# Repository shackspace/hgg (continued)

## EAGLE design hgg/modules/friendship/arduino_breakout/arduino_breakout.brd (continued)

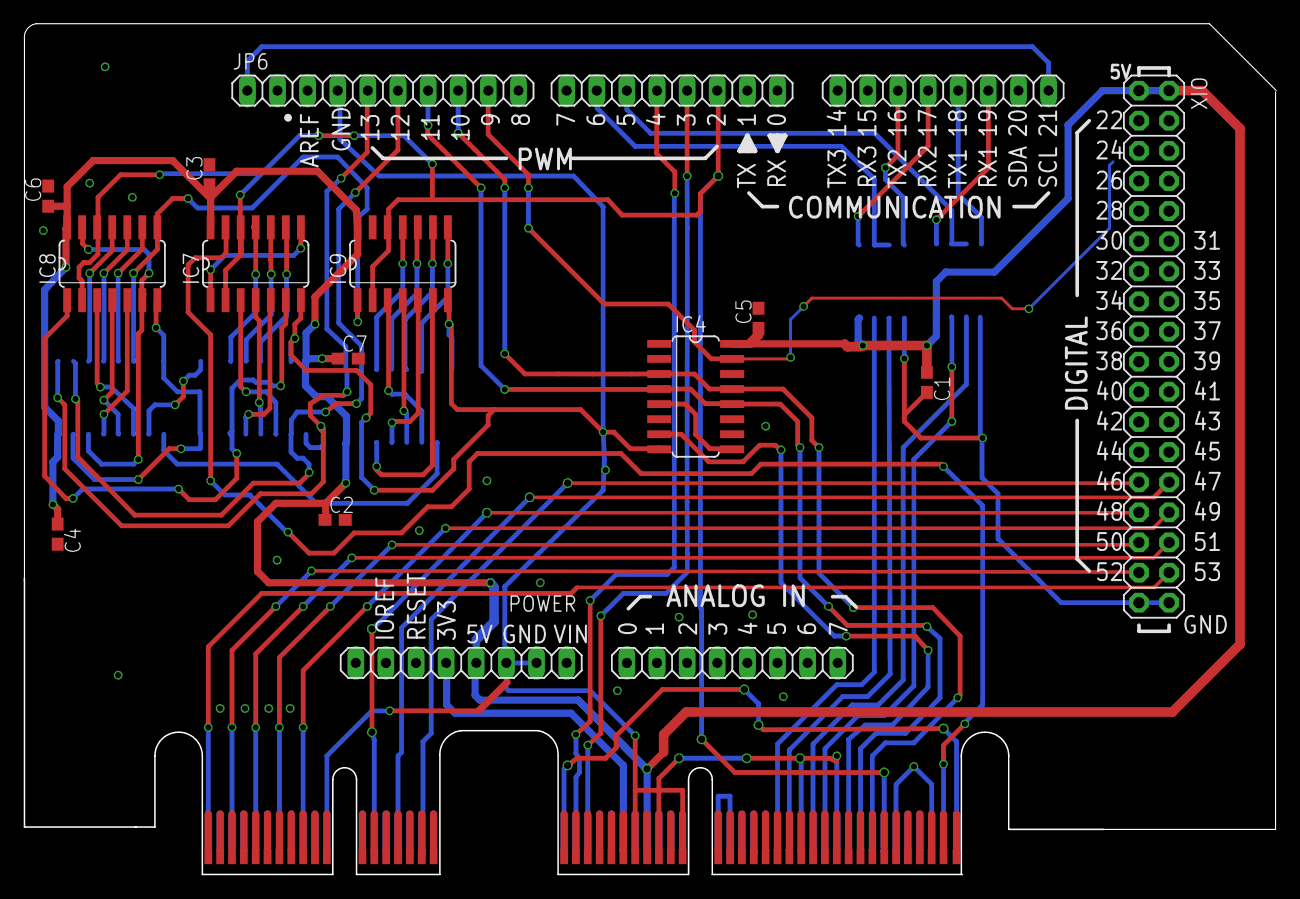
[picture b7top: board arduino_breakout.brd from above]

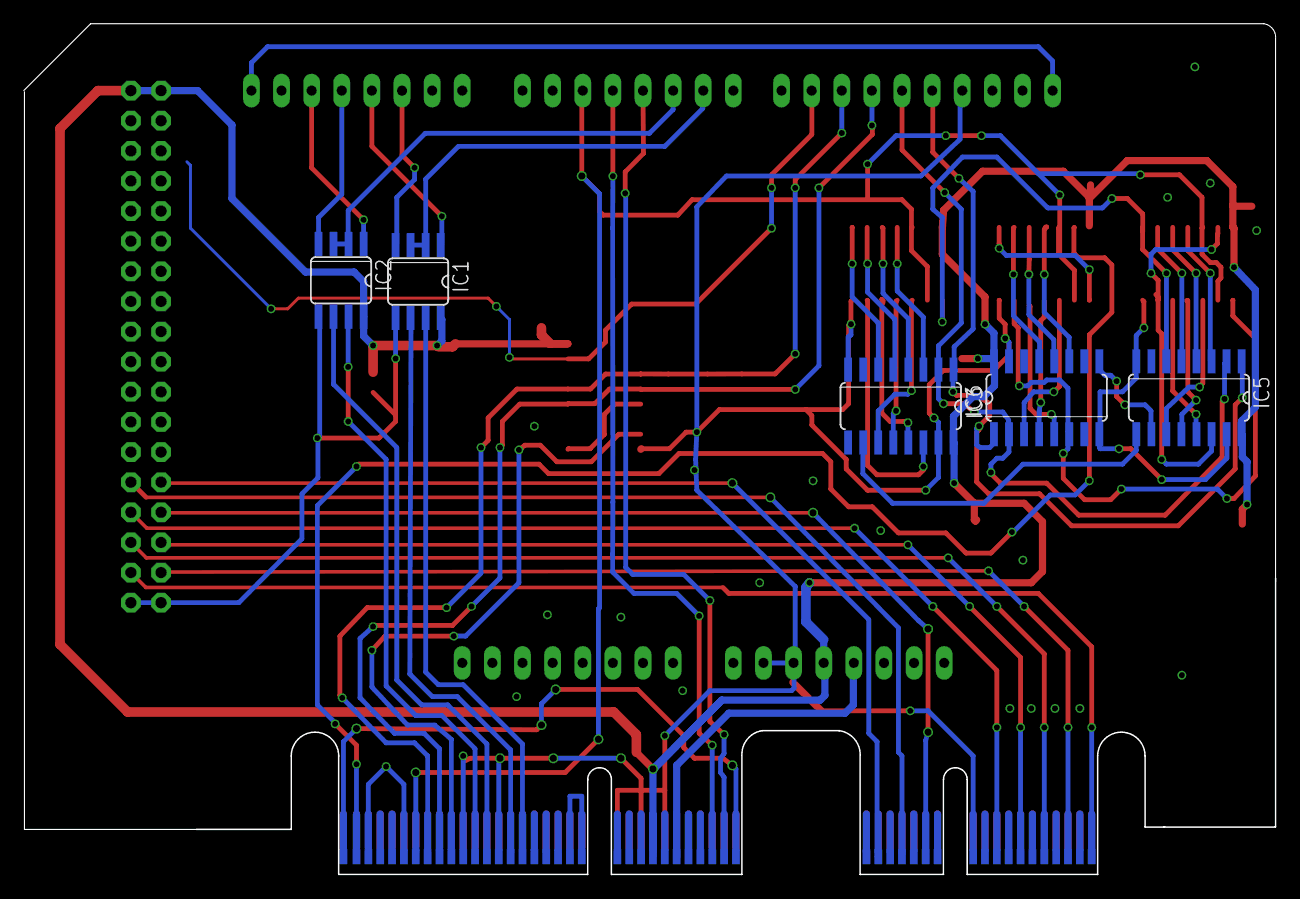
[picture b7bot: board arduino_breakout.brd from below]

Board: 2 copper layers, 105.6 x 71.7 mm, 23 parts (5 on the bottom side), 61 nets.

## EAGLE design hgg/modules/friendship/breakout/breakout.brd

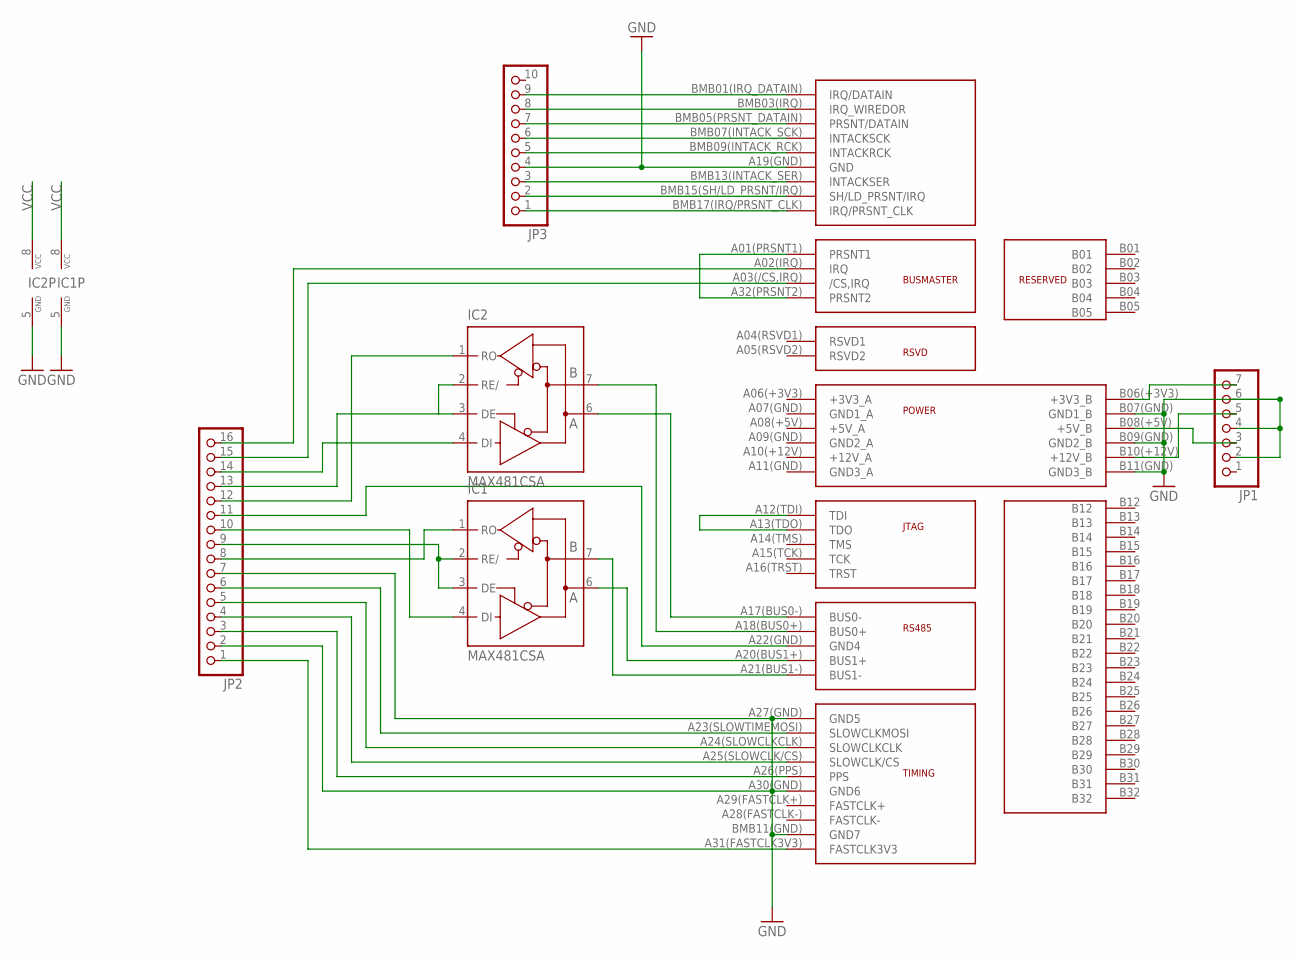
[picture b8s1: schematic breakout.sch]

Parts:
IC1, IC2: MAX481CSA; SO08
JP1: PINHD-1X7; 1X07
JP2: PINHD-1X16; 1X16
JP3: PINHD-1X10; 1X10
U$1: BUSMASTER; BUSMASTER_EDGE_CONNECTOR

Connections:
3V3: JP1.7, U$1.B06(+3V3) (+3V3_B)
12V: JP1.5, U$1.B10(+12V) (+12V_B)
GND: IC1.5 (GND), IC2.5 (GND), JP1.2, JP1.4, JP1.6, JP2.2, JP2.7, JP3.4, U$1.A19(GND) (GND), U$1.A27(GND) (GND5), U$1.A30(GND) (GND6), U$1.B07(GND) (GND1_B), U$1.B09(GND) (GND2_B), U$1.B11(GND) (GND3_B), U$1.BMB11(GND) (GND7)
unnamed: U$1.A01(PRSNT1) (PRSNT1), U$1.A32(PRSNT2) (PRSNT2)
unnamed: IC2.6 (A), U$1.A17(BUS0-) (BUS0-)
unnamed: IC2.7 (B), U$1.A18(BUS0+) (BUS0+)
unnamed: IC2.2 (RE/), IC2.3 (DE), JP2.13
unnamed: JP2.16, U$1.A02(IRQ) (IRQ)
unnamed: JP2.15, U$1.A03(/CS,IRQ) (/CS,IRQ)
unnamed: IC1.6 (A), U$1.A20(BUS1+) (BUS1+)
unnamed: IC2.4 (DI), JP2.14
unnamed: IC1.7 (B), U$1.A21(BUS1-) (BUS1-)
unnamed: JP2.11, U$1.A22(GND) (GND4)
unnamed: IC1.2 (RE/), IC1.3 (DE), JP2.9
unnamed: U$1.A12(TDI) (TDI), U$1.A13(TDO) (TDO)
unnamed: JP3.1, U$1.BMB17(IRQ/PRSNT_CLK) (IRQ/PRSNT_CLK)
unnamed: IC2.1 (RO), JP2.12
unnamed: IC1.1 (RO), JP2.8
unnamed: IC1.4 (DI), JP2.10
unnamed: JP2.6, U$1.A23(SLOWTIMEMOSI) (SLOWCLKMOSI)
unnamed: JP3.2, U$1.BMB15(SH/LD_PRSNT/I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 (SH/LD_PRSNT/IRQ)
unnamed: JP2.5, U$1.A24(SLOWCLKCLK) (SLOWCLKCLK)
unnamed: JP2.4, U$1.A25(SLOWCLK/CS) (SLOWCLK/CS)
unnamed: JP2.3, U$1.A26(PPS) (PPS)
unnamed: JP3.3, U$1.BMB13(INTACK_SER) (INTACKSER)
unnamed: JP2.1, U$1.A31(FASTCLK3V3) (FASTCLK3V3)
unnamed: JP3.5, U$1.BMB09(INTACK_RCK) (INTACKRCK)
unnamed: JP3.6, U$1.BMB07(INTACK_SCK) (INTACKSCK)
unnamed: JP3.7, U$1.BMB05(PRSNT_DATAIN) (PRSNT/DATAIN)
unnamed: JP3.8, U$1.BMB03(IRQ) (IRQ_WIREDOR)
unnamed: JP3.9, U$1.BMB01(IRQ_DATAIN) (IRQ/DATAIN)
VCC: IC1.8 (VCC), IC2.8 (VCC), JP1.3, U$1.B08(+5V) (+5V_B)

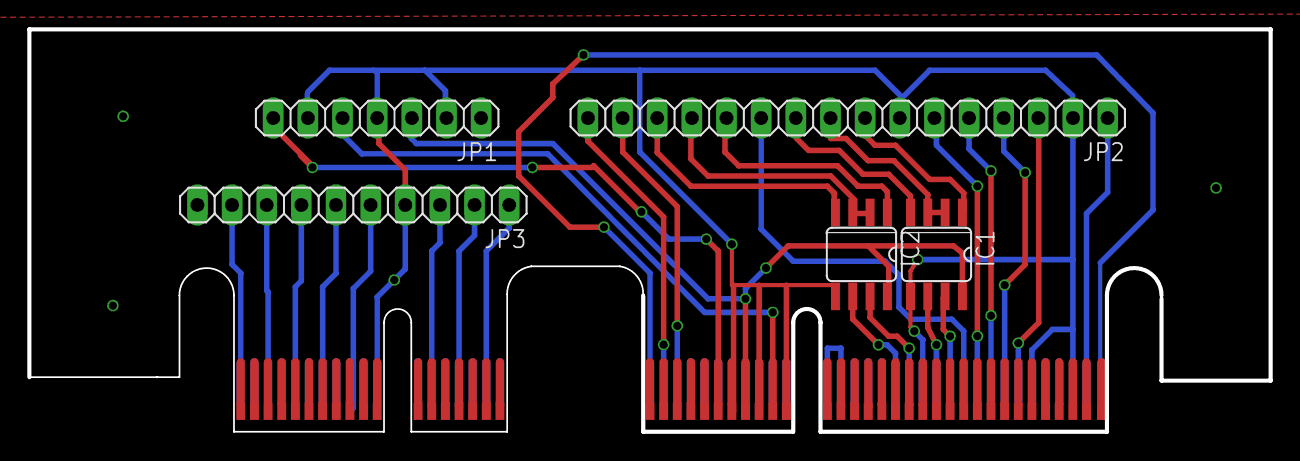
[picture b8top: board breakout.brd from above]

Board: 2 copper layers, 91.0 x 29.5 mm, 6 parts (0 on the bottom side), 32 nets.

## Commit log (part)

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2011-11-01 added dcf77 clocksource
2011-11-01 some tweaks and bugfixes so that the software finds the timings better
2011-11-01 added some more documentation
2011-11-01 added the README
2011-11-01 added some primitive code for dcf77 decoding. It's missing performance, does not perform consistency checks and was made just for proof of concept.
2011-11-20 we can haz better dcf77.
2011-11-20 test
2011-11-20 notes on getting it to work is more verbose.
2011-11-27 gauss loesungsalgorithmus von andreas eingecheckt.
2011-12-29 documentation linked in readme
2012-01-17 to -> too :)
2012-02-05 new version of flutter module, initial version, compiles vhdl nwo
2012-02-05 correct bit counts
2012-02-05 initial commit: schematic and layout of timing fpga board (unfished)
2012-02-05 added reference design: sparkfun fpga breakoutboard
2012-02-09 schematic for power board
2012-02-09 started working on braeburn board design
2012-02-09 routing optimization
2012-02-10 working on schematic: voltage regulators are completed, working on JTAG Port
2012-02-11 added PCIe-X-4 Connector for friendship
2012-02-11 initial version of PCI-e x4 edge connector added
2012-02-11 done for now
2012-02-15 minor change: analog groundplane has a bit more distance to the other groundplanes.
2012-02-16 added tool for utc / unixtime conversion
2012-02-17 fixed my fail on use of a zdiode (thanks to samuel), and stuff
2012-02-18 added logos
2012-02-25 friendship edge connector final
2012-02-26 we started working on friendship schematics
2012-02-26 as far as i got tonight
2012-02-28 bugfix
2012-03-03 Added friendship connector to board and changed FPGA type from XC3S50VQ100 to XC3S50AVQ100
2012-03-09 removed dublicate pinmappings
2012-03-17 changed pinouts around and rounted friendship
2012-03-18 connected FPGA to friendship connector
2012-03-25 added atmega8 to flutter board
2012-03-26 added RS485 level converter and 8MHz crystal to board (for uController)
2012-03-31 organized parts of schematic by function finished routing, some power pins are not connected
2012-04-01 added hgg logo as a part
2012-04-01 layout aimed at regular manufacturing processes
2012-04-01 cleanup. emergency commit
2012-04-01 added hgg logo as a device
2012-04-01 added license information, top groundplane, minor routing cleanups
2012-04-01 connected all the signals to wires just gps module is missing on the board
2012-04-01 merged hgg.lbr from friendship_v_1 branch to master
2012-04-01 applied changed in hgg.lbr to the board, added ground planes
2012-04-01 we have two differential bus pairs with rs485
2012-04-01 fixed wrong routing for differential bus pairs
2012-04-04 minor trace improvements
2012-04-05 added GPS module to hgg.lbr and circuit of fpga timing board
2012-04-06 breakout board for friendship connectors
2012-04-07 design rules
2012-04-08 current status
2012-04-10 moved busmaster plug
2012-04-14 friendship card layout uses dimension now for the outlines which means the card will be milled in production
2012-04-14 minor improvements, thicker power lines
2012-04-21 slight update
2012-04-22 learned things from making the pcb
2012-04-25 Added testpoints
2012-04-26 braeburn version
2012-04-27 new braeburn version for using a PC ps
2012-04-28 changes to solve problems with the first design
2012-04-28 added custom DRU for hgg boards
2012-04-29 design failed
2012-04-29 new try with power saving
2012-04-29 braeburn v1... so far
2012-04-30 current braeburn board layout
2012-04-30 improvements on the design
2012-05-02 added mq303a alcohol sensor from seeedstudio
2012-05-02 update pin layout / rotation
2012-05-04 this is the pinout you get most often.
2012-05-05 some traces of braeburn1 are 20% cooler now
2012-05-06 routes are 20% cooler now
2012-05-06 added a bunch of datasheets for parts we are using
2012-05-06 added analog switch datasheet
2012-05-06 placed busmaster plug better on the breakout. fixes issue.
2012-05-06 added more parts
2012-05-06 added .. something
2012-05-06 added libre office lock file
2012-05-06 some cleanup of the presentation 20120510_cccs
2012-05-06 obsolet file appendix.tex removed
2012-05-06 some improvements on sides with pictures all content itemeized
2012-05-07 added some item tags and added physical spec items
2012-05-07 added items for all status quo frames
2012-05-07 fixed case
2012-05-07 fixed cased, added items
2012-05-08 added more items
2012-05-08 removed an old line which was double
2012-05-08 fixed punctuation and case
2012-05-08 renamed file
2012-05-08 removed old content
2012-05-09 more content and formatting
2012-05-09 information about constellation and applications, consolidating existing info
2012-05-09 added caveat and info
2012-05-09 added a few more images
2012-05-09 missing image
2012-05-09 even more images
2012-05-09 good seller, will buy again
2012-05-09 added measure as pdf
2012-05-09 added images for measure and accuracy
2012-05-09 added hgg logo
2012-05-10 added some further clarifications after the press feedback frame
2012-05-10 changed column width to 0.3. added "first idea" slide
2012-05-10 beamer, Y U SO COMPLICATED
2012-05-10 compiled PDFs
2012-05-12 deleted
2012-05-12 added gitignore
2012-05-12 added repostructure
2012-05-12 slides for thundertalks at shackspace
2012-05-12 deleted unneeded files
2012-05-12 renamed toplevel software to applications
2012-05-12 moved eagle folder to hgg/libs
2012-05-12 moved dcf77 to hgg/modules/obsolete
2012-05-12 moved readme to dcf77
2012-05-12 moved modules
2012-05-12 moved flutter0 to firmware/timing_fpga
2012-05-12 now it is the proper structure
2012-05-12 added image and a few slides
2012-05-13 started working on the testing of the testsuite
2012-05-13 reads test definitions
2012-05-13 added unit test
2012-05-13 cleaned the buildsystem and added more structure to it.
2012-05-13 just a test
2012-05-13 added second integration test for checking the testsdescriptions for validity.
2012-05-16 added cheaper alternative to the expensive max485 bus driver
2012-05-16 added PCIe 1x slot
2012-05-16 changed package of resistors and capasitors to 0603 added values
2012-05-17 added pinout of busmaster port
2012-05-17 fixed a bug: shift enable must be defaulted to low
2012-05-17 swapped sides of the pcb
2012-05-18 few improvements
2012-05-20 fixed issue #27: moved signals to the other side of friendship connector
2012-05-20 changed supply of rs485 transciever to 5V
2012-05-23 flutter pcb is ready for review
2012-05-28 addede copyright txt, will be changed in future
2012-05-28 added template white on black
2012-06-04 Added adsb2spi Verilog module.
2012-06-08 added pullups to IRQ lines
2012-06-08 moved diodes next to PCIe connector, rerouting, IRQ pullups now on bottom
2012-06-16 moved holes for pci-e x4 plug to match the actual parts...
2012-06-16 added pcie x1 slot
2012-06-16 pinning for breakout edge connectors
2012-06-16 added devices for the new functionality
2012-06-17 using new busmaster plug, more ground vias
2012-06-22 increased resttring from 0 to 25%. fixed DRC issues
2012-06-22 added first version of friendship design documentation
2012-06-27 arduino breakout, without timing
2012-06-29 arduino breakout
2012-06-29 applied high spec dru
2012-06-29 applied high spec dru (after merge)
2012-07-07 applied DRCs, not all passing, minor routing improvements, increased trace width
2012-07-07 ran DRC, no errors
2012-07-07 ran DRC, not all passing (PCIe conn), fixed wire width issues, some routing improvements
2012-07-07 added dimensions
2012-07-13 fixed symbol "friendship connector": some connectors were offgrid
2012-07-15 schematic for what's on the experiment now
2012-07-18 changed to use DIL chips
2012-07-31 fixed solder stop layer of friendschip connector
2012-07-31 new release of braeburn board file
2012-08-04 adding a 3D-printable fixation for the connected boards
2012-10-05 improved layout
2012-10-05 layout improvements
2012-10-16 visibility
2012-10-27 first version of spaceup talk
2012-10-27 PDf renderings
2012-10-27 added build system for arduino libraries into magic
2012-10-27 started make system for multiple platforms
2012-10-27 added the first testcase for sipo register
2012-10-27 got serial ports working
2012-10-27 compiles and uploads to the uc
2012-10-27 added test for the wired or
2012-10-27 file is unneeded now
2012-10-27 added test for the IRQ piso
2012-10-27 added test for chipselect register
2012-10-27 added interface to programming the mac layer
2012-10-27 moar
2012-10-27 fiddled around with the stuff. found bugs in pull ups with the IRQs.
2012-10-27 changed tests to work with three breakouts for arduino
2012-10-27 enabled all tests
2012-10-27 added tests for rs485
2012-10-27 added more verbose output if a test fails.
2012-10-27 implemented first two busmaster tests
2012-10-27 cleanup paths
2012-10-27 mock for physical bus before developing the protocol layer
2012-10-27 renamed test, added message queue
2012-10-27 added missing file
2012-10-27 magic bytes changed to be 1010... in binary
2012-10-27 the mock, it compiles!
2012-10-27 added bus message implementation
2012-10-27 began implementing communication
2012-10-27 added test to verify struct BusMessage integrity
2012-10-27 moved eBusMessageType out of struct BusMessageRaw, made BusMessageRaw methods and parameters const where possible
2012-10-27 removed file no longer needed
2012-10-27 added class BusMessage to wrap actual dynamic sized message buffers and refactored the buffer accessor helper to BusMessageRaw
2012-10-27 refactoring of dynamic size structure, adding method to determine type-based size of required buffer
2012-10-27 names makefile makefile.generated
2012-10-27 changed path to header
2012-10-27 first try to implement a communication reply
2012-10-27 extracted BusMessagePayload accessor and refactored BusMessage to return this as well
2012-10-27 refactored struct BusMessageRaw usage to use class BusMessage instead
2012-10-27 adapted test to refactored BusMessage
2012-10-29 renamed files to new abstraction model
2012-10-29 switching over to gmock and gtest, learning as we go
2012-10-29 properly initializing gtest
2012-10-29 added .gitignore
2012-10-31 added gmock install bootstrap script
2012-10-31 deprecated dedicated busmaster subfolder
2012-10-31 added include guard
2012-10-31 mock for BusmasterCardPHY
2012-10-31 renamed include guard
2012-10-31 added rudimentary BusmasterCardLogicImpl based on CardLogicImpl
2012-10-31 busmastercard is now equivalent to card
2012-11-01 added BMCLIS_Enumerate state
2012-11-02 migrated to google test
2012-11-02 updated path for hardware tests
2012-11-02 compiletime configuration files
2012-11-02 blackplane + tests
2012-11-02 magic commit: enumeration happy path test implemented.
2012-11-04 refactored busmastercardphy interface to be more conistent regarding naming of message handling function
2012-11-11 added timeout mechanism during the bus enumeration
2012-11-11 added code for send message request (card2card), happy path
2012-11-17 avr makefile
2012-11-17 added helper script to run all software tests
2012-11-17 less talkative makefiles
2012-11-17 less talkative now
2012-11-17 expluded items from build which are not currently needed
2012-11-17 avr-gcc does not like our initializer list, using placement new instead
2012-11-17 now also cleaning preprocessor output
2012-11-17 added defines for slot selection IDs and MASKs
2012-11-18 the tests, there are so many
2012-11-18 added more arduino specific compile switches
2012-12-02 removed deprecated files
2012-12-02 renamed folder to reflect arduino naming scheme
2012-12-02 more adjustments for the new folder structure
2012-12-02 proper casing
2013-01-12 updates versoin of braeburn
2013-01-12 moved adsb2spi to dash folder and added xcr3064xl breakout board
2013-01-12 moved testboards folder to hardware folder
2013-01-12 reduced component count, TLC: replaced TRT with SMD variant, layout redone
